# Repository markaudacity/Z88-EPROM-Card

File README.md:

# Z88 EPROM Card
128kB EPROM board for the Cambridge Z88, based on XavSnap's design.<br />
This version has the correct pin spacing for the edge connector (courtesy of [Jim Conner](github.com/jimconner))

&emsp;

# Current Status
The only circuit change made was the replacement of the connector footprint and the fixing of a silkscreen typo, so the board should work as it sits, but I have not personally built and tested one so YMMV.

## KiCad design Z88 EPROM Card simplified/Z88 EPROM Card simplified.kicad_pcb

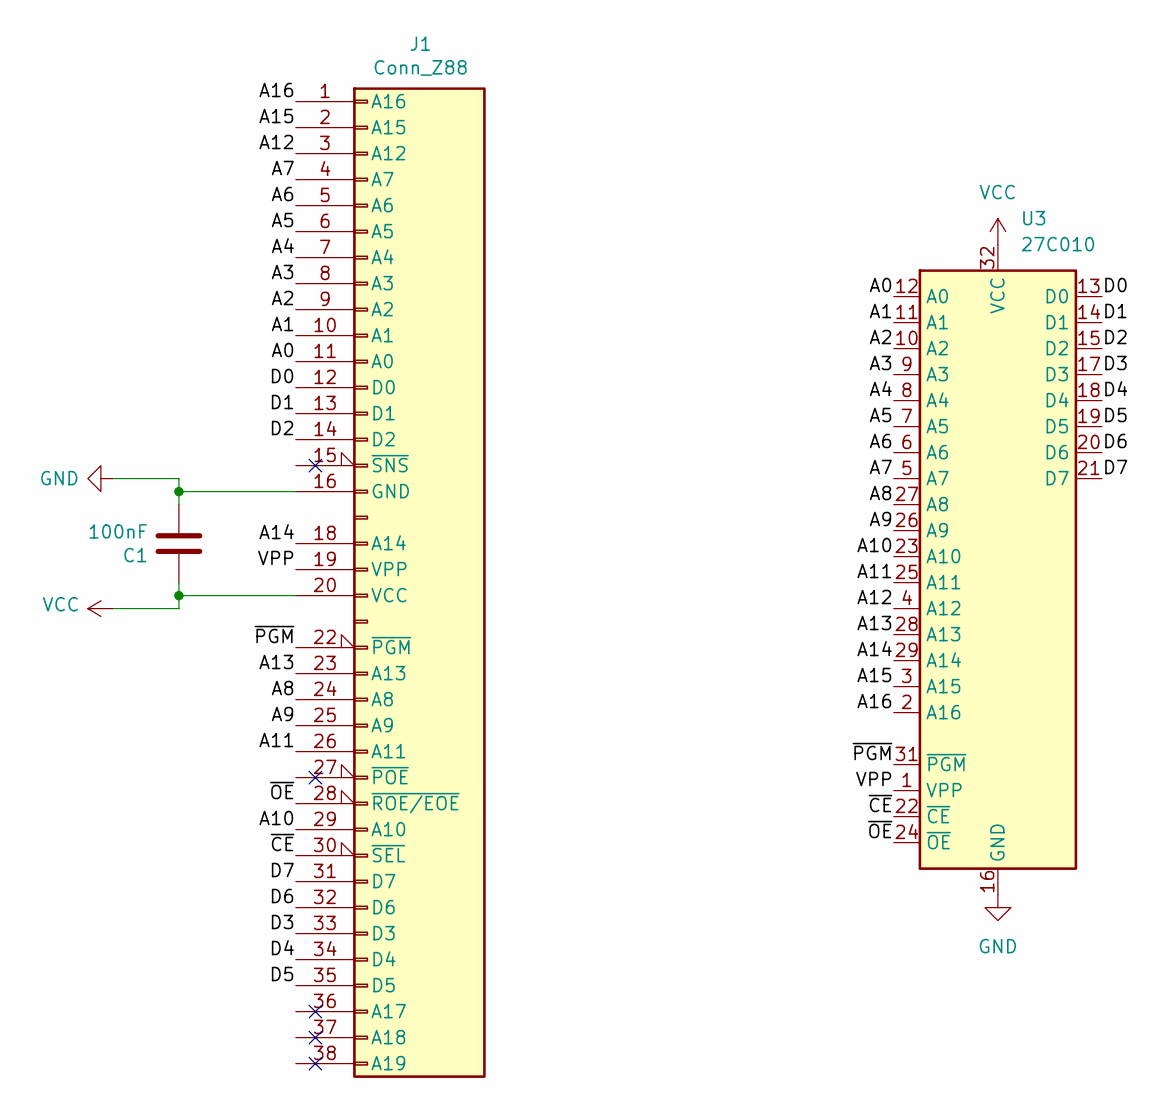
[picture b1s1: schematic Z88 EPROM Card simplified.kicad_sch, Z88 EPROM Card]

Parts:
C1: 100nF; C_Disc_D5.1mm_W3.2mm_P5.00mm
J1: Conn_Z88; Z88_Card_BONDED PADS
U3: 27C010; DIP-32_W15.24mm_LongPads

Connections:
/A0: J1.11 (A0), U3.12 (A0)
/A1: J1.10 (A1), U3.11 (A1)
/A2: J1.9 (A2), U3.10 (A2)
/A3: J1.8 (A3), U3.9 (A3)
/A4: J1.7 (A4), U3.8 (A4)
/A5: J1.6 (A5), U3.7 (A5)
/A6: J1.5 (A6), U3.6 (A6)
/A7: J1.4 (A7), U3.5 (A7)
/A8: J1.24 (A8), U3.27 (A8)
/A9: J1.25 (A9), U3.26 (A9)
/A10: J1.29 (A10), U3.23 (A10)
/A11: J1.26 (A11), U3.25 (A11)
/A12: J1.3 (A12), U3.4 (A12)
/A13: J1.23 (A13), U3.28 (A13)
/A14: J1.18 (A14), U3.29 (A14)
/A15: J1.2 (A15), U3.3 (A15)
/A16: J1.1 (A16), U3.2 (A16)
/D0: J1.12 (D0), U3.13 (D0)
/D1: J1.13 (D1), U3.14 (D1)
/D2: J1.14 (D2), U3.15 (D2)
/D3: J1.33 (D3), U3.17 (D3)
/D4: J1.34 (D4), U3.18 (D4)
/D5: J1.35 (D5), U3.19 (D5)
/D6: J1.32 (D6), U3.20 (D6)
/D7: J1.31 (D7), U3.21 (D7)
/VPP: J1.19 (VPP), U3.1 (VPP)
/~CE: J1.30 (~SEL), U3.22 (~CE)
/~OE: J1.28 (~ROE/EOE), U3.24 (~OE)
/~PGM: J1.22 (~PGM), U3.31 (~PGM)
GND: C1.2, J1.16 (GND), U3.16 (GND)
VCC: C1.1, J1.20 (VCC), U3.32 (VCC)

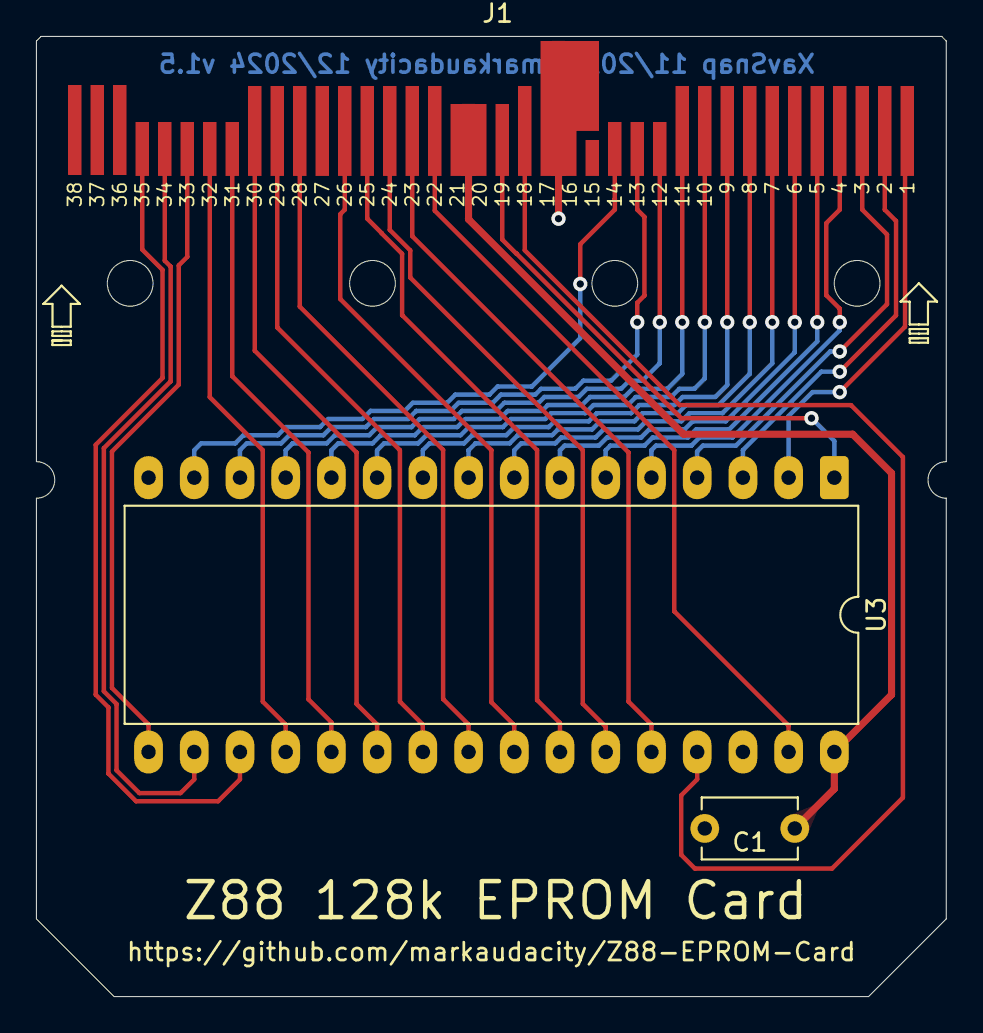
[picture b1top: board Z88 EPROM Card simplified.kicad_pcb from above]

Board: 2 copper layers, 50.5 x 53.3 mm, 3 parts (0 on the bottom side), 31 nets.

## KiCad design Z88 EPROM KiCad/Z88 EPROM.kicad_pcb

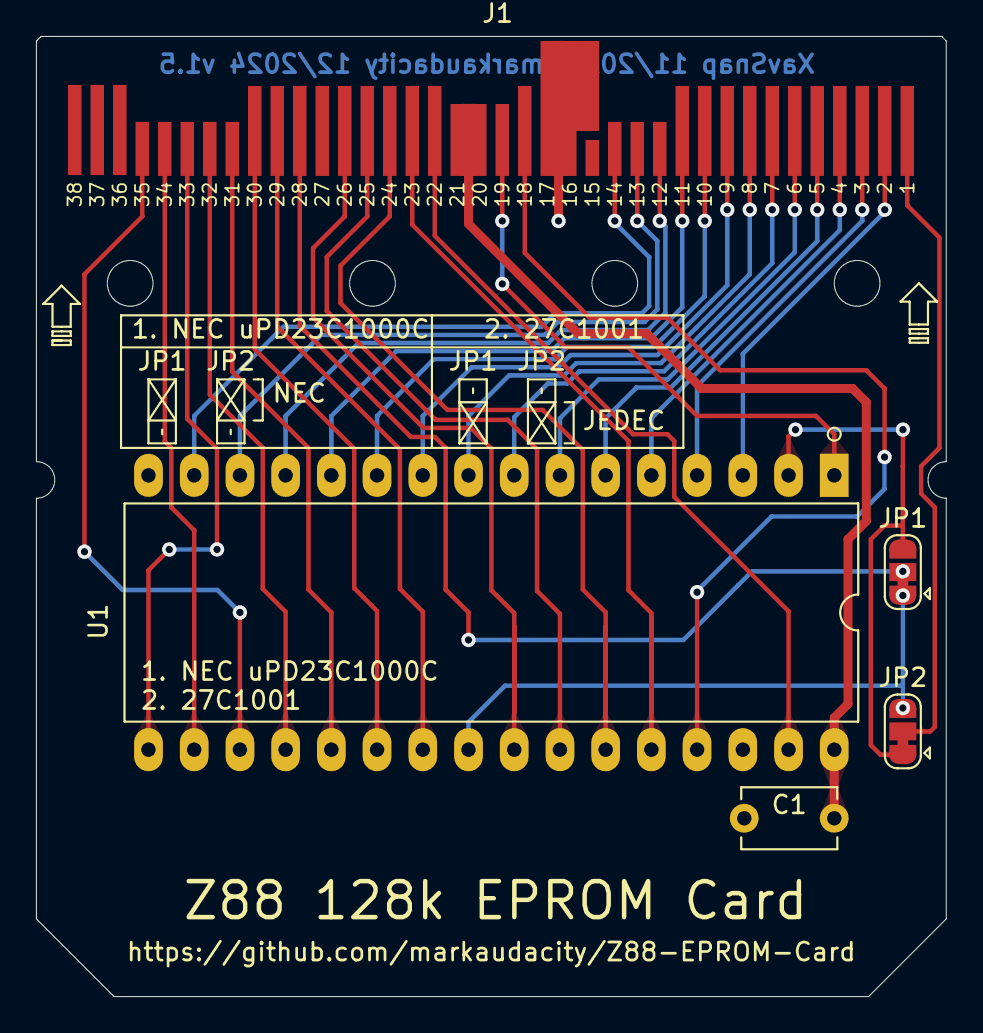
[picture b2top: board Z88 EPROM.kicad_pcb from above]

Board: 2 copper layers, 50.5 x 53.3 mm, 5 parts (0 on the bottom side), 33 nets.

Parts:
C1: 100nF; C_Disc_D5.1mm_W3.2mm_P5.00mm
J1: Conn_Z88; Z88_Card_BONDED PADS
JP1, JP2: NEC/JEDEC; SolderJumper-3_P1.3mm_Bridged12_RoundedPad1.0x1.5mm
U1: NEC_ROM; DIP-32_W15.24mm_LongPads

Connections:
/A0: J1.11 (A0), U1.12 (A0)
/A1: J1.10 (A1), U1.11 (A1)
/A2: J1.9 (A2), U1.10 (A2)
/A3: J1.8 (A3), U1.9 (A3)
/A4: J1.7 (A4), U1.8 (A4)
/A5: J1.6 (A5), U1.7 (A5)
/A6: J1.5 (A6), U1.6 (A6)
/A7: J1.4 (A7), U1.5 (A7)
/A8: J1.24 (A8), U1.27 (A8)
/A9: J1.25 (A9), U1.26 (A9)
/A10: J1.29 (A10), U1.23 (A10)
/A11: J1.26 (A11), U1.25 (A11)
/A12: J1.3 (A12), U1.4 (A12)
/A13: J1.23 (A13), U1.28 (A13)
/A14: J1.18 (A14), U1.29 (A14)
/A15: J1.2 (A15), U1.3 (A15)
/A16: J1.1 (A16), JP1.2
/D0: J1.12 (D0), U1.13 (D0)
/D1: J1.13 (D1), U1.14 (D1)
/D2: J1.14 (D2), U1.15 (D2)
/D3: J1.33 (D3), U1.17 (D3)
/D4: J1.34 (D4), U1.18 (D4)
/D5: J1.35 (D5), U1.19 (D5)
/D6: J1.32 (D6), U1.20 (D6)
/D7: J1.31 (D7), U1.21 (D7)
/ROE: J1.28 (~ROE/EOE), JP2.2
/Vpp: J1.19 (VPP), U1.1 (VPP)
/WEL: J1.22 (~WE/PGM), U1.31 (PGM)
/~SE1: J1.30 (~CE), U1.22 (CE)
GND: C1.1, J1.16 (GND), U1.16 (GND)
unnamed: JP1.1, JP2.3, U1.24 (A16)
unnamed: JP1.3, JP2.1, U1.2 (ROE)
VCC: C1.2, J1.20 (VCC), U1.32 (VCC)

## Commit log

2025-01-03 README
2025-01-06 upload KiCad files
    was waiting to get permission from XavSnap to share my modifications
2025-01-06 added images
2025-01-06 added images to readme
2025-01-06 deleted superfluous
2025-01-06 finally destroying 1.27mm connector
2025-01-06 fixed trace connections to edge connector
2025-01-06 reorganize
2025-01-13 removed backups from git
2025-01-13 added PDF schematic, misc file cleanup, silkscreen tweaks
2025-01-13 deleted: XavSnap EPROM v1.5-backups/XavSnap EPROM v1.5-2025-01-12_003050.zip
2025-01-14 cleanup
2026-03-19 simplified version
